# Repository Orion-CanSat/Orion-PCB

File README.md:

# Orion II PCB

&nbsp;
## Who are we?
We are a team composed of 12 students of the [Model High School “Evangeliki Scholi Smyrna”](http://lyk-evsch-n-smyrn.att.sch.gr/wordpress/?p=1322). For the fourth consecutive time we are participating in the Panhellenic competition "[CanSat in Greece](https://cansat.gr/)", a qualifier of the Pan-European competition "[CanSats in Europe](http://www.esa.int/SPECIALS/CanSat/SEMXTDCKP6G_0.html)", organized by ESA (European Space Agency) for the last 8 years. Our team is called Orion II and our supervisor is Dr. Christos Fanidis.

&nbsp;
## Our Inspiration

&nbsp;
## Do you want to contibute?
Unfortuannately this repository does not accept any new commits, or merge requests. You are free to fork it and work on your own.

&nbsp;
## PCB Desgin
These PCBs where designed by Danae Veli.

&nbsp;
## Meet our Team (In alphabetical order)
|                                Name                                |                              Role                              |                                                                                                                                     Introduction                                                                                                                                    |
| ------------------------------------------------------------------ | -------------------------------------------------------------- | ----------------------------------------------------------------------------------------------------------------------------------------------------------------------------------------------------------------------------------------------------------------------------------- |
|                           __Danae Veli__                           |                 Head of Electrical Engineering                 |                               My name is Danae Veli and I am a student at Model High School "Evangeliki Scholi Smyrna". I am a part of team Orion II and I am in charge of the electrical design. My main duty is to design the PCBs for the project.                               |
|   [__Dionysios Angelopoulos__](https://github.com/DennisAngelo)    | Head of Mechanical Engineering and Control Systems Development | My name is Dionysios Angelopoulos. I am a greek High School student attending Model High School “Evangeliki Scholi Smyrna”. I am the head of Mechanical Engineering in Orion II. My main duty was to 3D model the cansat and to design and tune the control system for the cansat.  |
|           [__Jim Balatos__](https://github.com/jbalatos)           |                  Head of Software Engineering                  |                           My name is Jim Balatos. I am a greek High School student attending Model High School “Evangeliki Scholi Smyrna”. I am the head of Software Engineering in Orion II. My main duty was to write the Live Server of our mission.                             |
|                         __Giorgos Kaltsis__                        |                       Senior Data Analyst                      |              |
| [__Konstantinos Kritharidis__](https://github.com/konstantinosk31) |                    Head of Retrieval System                    |               My name is Konstantinos Kritharidis. I am a greek High School student attending The American College of Greece - Pierce. I am the head of the Retrieval System in Orion II. My main duty was to design and create the ram-air parachute for the CanSat.               |
|       [__Rikarnto Bariampa__](https://github.com/richardbar)       |         Head of Telemetry and Senior Software Engineer         |               My name is Rikarnto Bariampa. I am a greek High School student attending Model High School “Evangeliki Scholi Smyrna”. I am the head of Telemetry and a Senior Software Engineer in Orion II. My main duty was to write the onboard code for the CanSat.              |

&nbsp;
## Want to reach us?
If you have any question, please feel free to reach us in one of the following ways:
* [__Email__](mailto:orioncantgr@gmail.com)
* [__Facebook__](https://www.facebook.com/orioncansatteam)
* [__Twitter__](https://twitter.com/OrionCanSat2020)

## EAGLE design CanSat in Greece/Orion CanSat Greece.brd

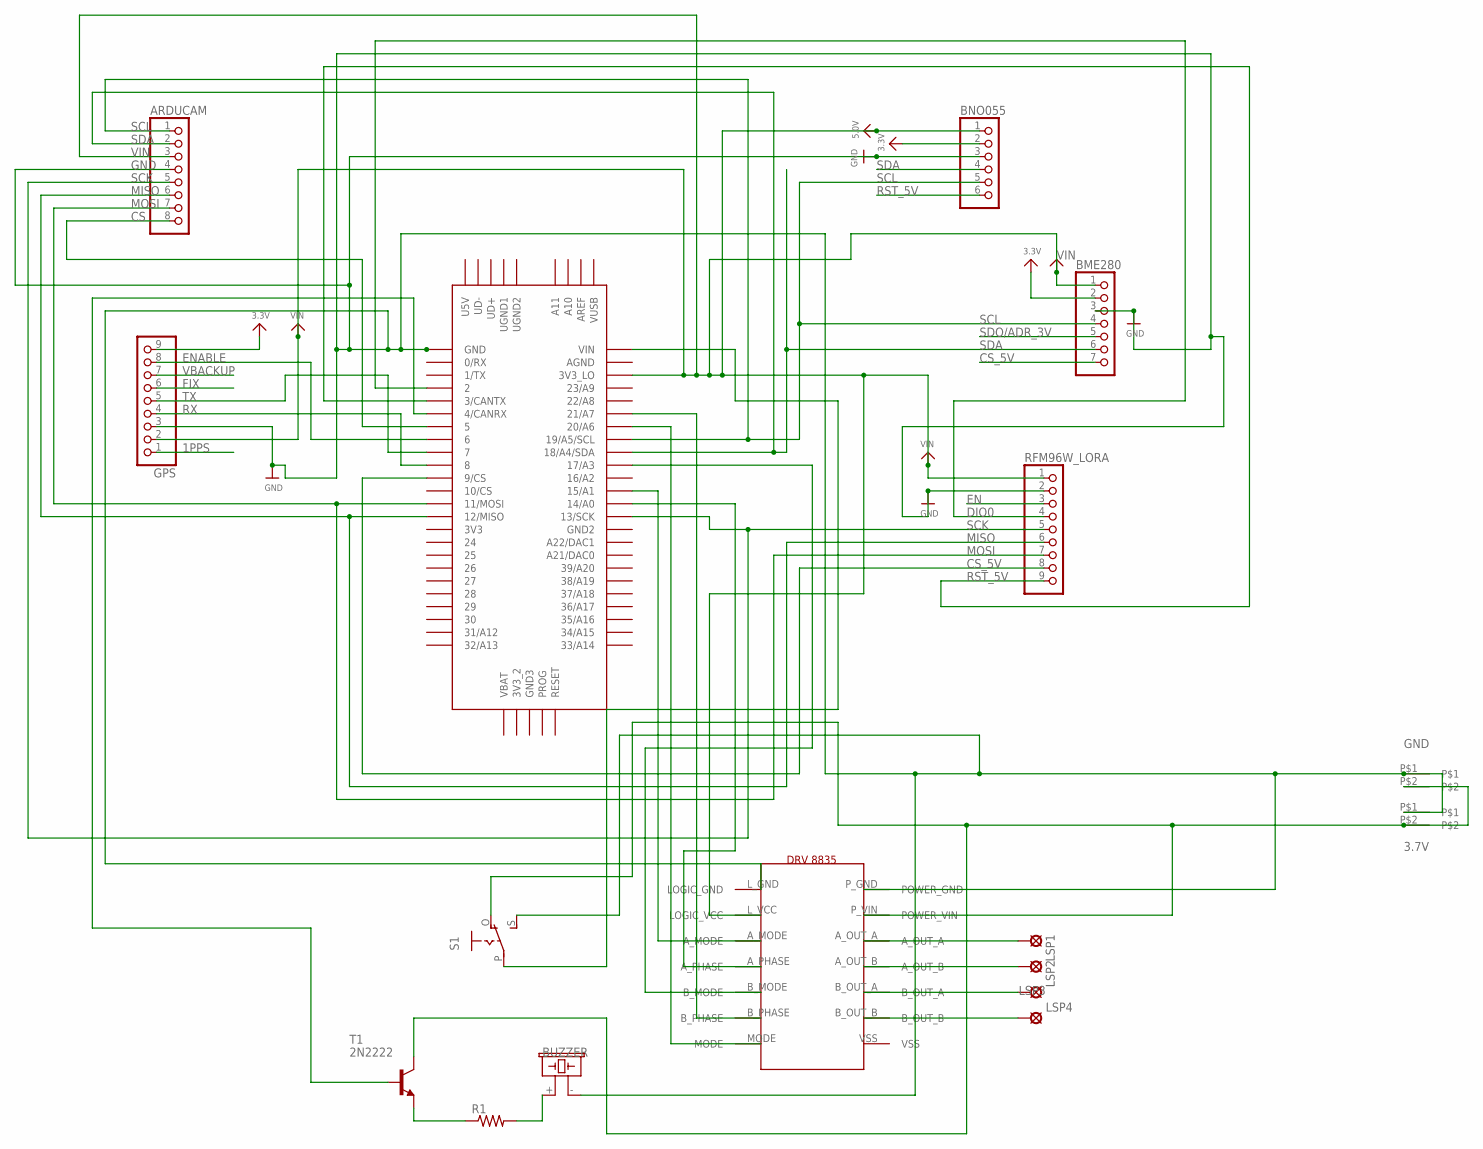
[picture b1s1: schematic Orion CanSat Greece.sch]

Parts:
ARDUCAM: PINHD-1X8BIG; 1X08-BIG
BME280: HEADER-1X770MIL; 1X07_ROUND_70
BNO055: HEADER-1X676MIL; 1X06_ROUND_76
GPS: HEADER-1X970MIL; 1X09_ROUND_70
LSP1, LSP2, LSP3, LSP4: LSP13
R1: FLIPFLOP-RES; 0805-THM
RFM96W_LORA: HEADER-1X970MIL; 1X09_ROUND_70
S1: EG1218S; EG1218
SG2: F/CM12P
T1: 2N2222; TO92-EBC-OVAL
U$1: TEENSY_3.5/3.6
U$7, U$8: 2PINS
U$15: DRV8835

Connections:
1PPS: GPS.1
3.3V: BME280.2, BNO055.2, GPS.9
3V7: S1.P, U$1.VIN
BZPWR: R1.2, SG2.+ (1)
CS: ARDUCAM.8, U$1.5
CS_5V: BME280.7, RFM96W_LORA.8, U$1.9/CS
DIO0: RFM96W_LORA.4, U$1.2
EN: RFM96W_LORA.3
ENABLE: GPS.8, U$1.6
FIX: GPS.6
GND: ARDUCAM.4, BME280.3, BNO055.3, GPS.3, RFM96W_LORA.2, S1.S, SG2.- (2), U$1.GND, U$7.P$1, U$8.P$1, U$15.L_GND (LOGIC_GND), U$15.P_GND (POWER_GND)
MISO: ARDUCAM.6, RFM96W_LORA.6, U$1.12/MISO
MOSI: ARDUCAM.7, RFM96W_LORA.7, U$1.11/MOSI
unnamed: R1.1, T1.E
unnamed: U$1.20/A6, U$15.MODE
unnamed: T1.B, U$1.4/CANRX
unnamed: U$1.21/A7, U$15.B_PHASE
unnamed: U$1.14/A0, U$15.A_PHASE
unnamed: U$1.15/A1, U$15.A_MODE
unnamed: U$1.17/A3, U$15.B_MODE
unnamed: LSP1.MP, U$15.A_OUT_A
unnamed: LSP2.MP, U$15.A_OUT_B
unnamed: LSP3.MP, U$15.B_OUT_A
unnamed: LSP4.MP, U$15.B_OUT_B
RST_5V: BNO055.6, RFM96W_LORA.9, U$1.3/CANTX
RX: GPS.4, U$1.8
SCK: ARDUCAM.5, RFM96W_LORA.5, U$1.13/SCK
SCL: ARDUCAM.1, BME280.4, BNO055.5, U$1.19/A5/SCL
SDA: ARDUCAM.2, BME280.6, BNO055.4, U$1.18/A4/SDA
SDO/ADR_3V: BME280.5
TX: GPS.5, U$1.7
VBACKUP: GPS.7
VBAT: S1.O, T1.C, U$7.P$2, U$8.P$2, U$15.P_VIN (POWER_VIN)
VIN: ARDUCAM.3, BME280.1, BNO055.1, GPS.2, RFM96W_LORA.1, U$1.3V3_LO, U$15.L_VCC (LOGIC_VCC)

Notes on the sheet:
3.7V
GND
BUZZER
VIN

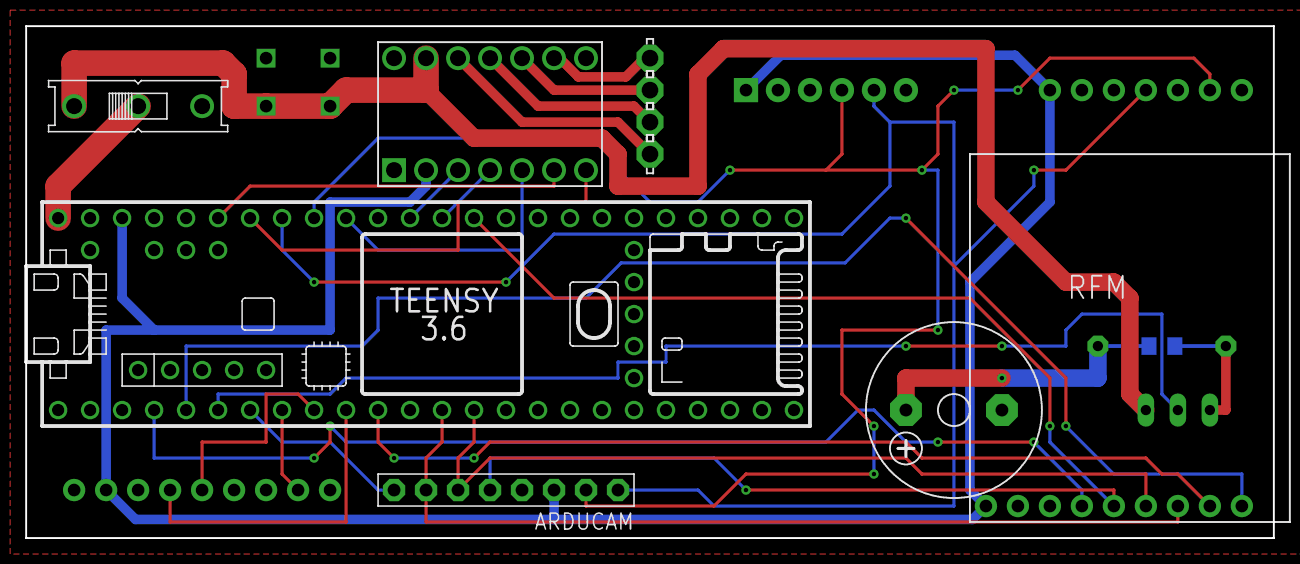
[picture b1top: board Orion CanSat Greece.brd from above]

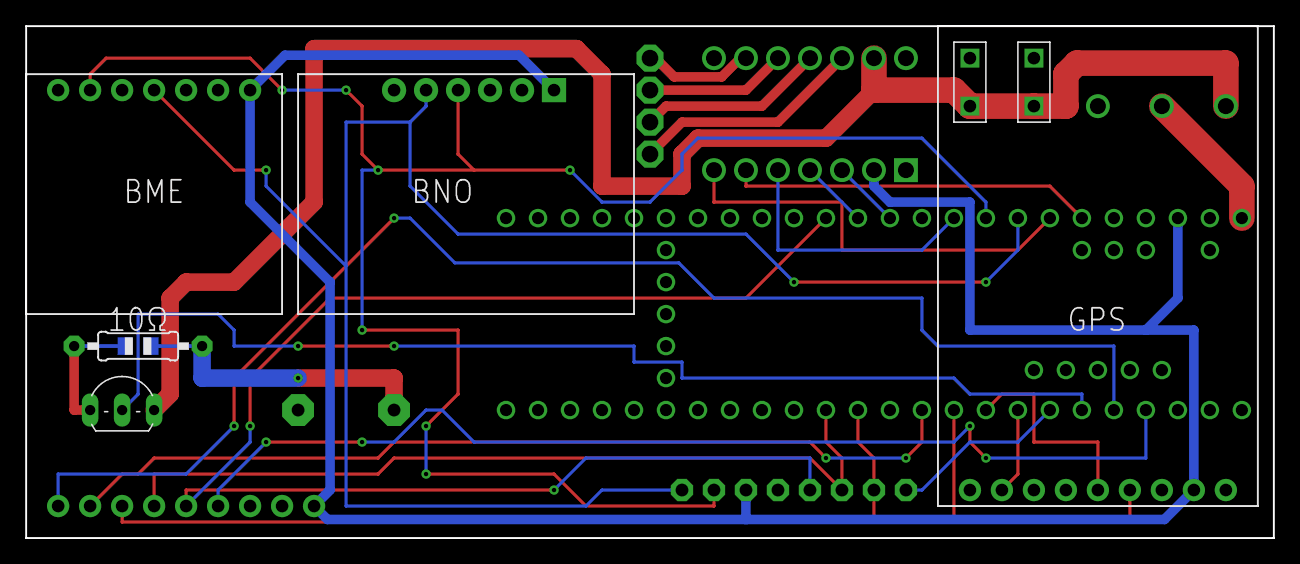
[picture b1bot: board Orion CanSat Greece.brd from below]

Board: 2 copper layers, 99.1 x 40.6 mm, 17 parts (4 on the bottom side), 29 nets.

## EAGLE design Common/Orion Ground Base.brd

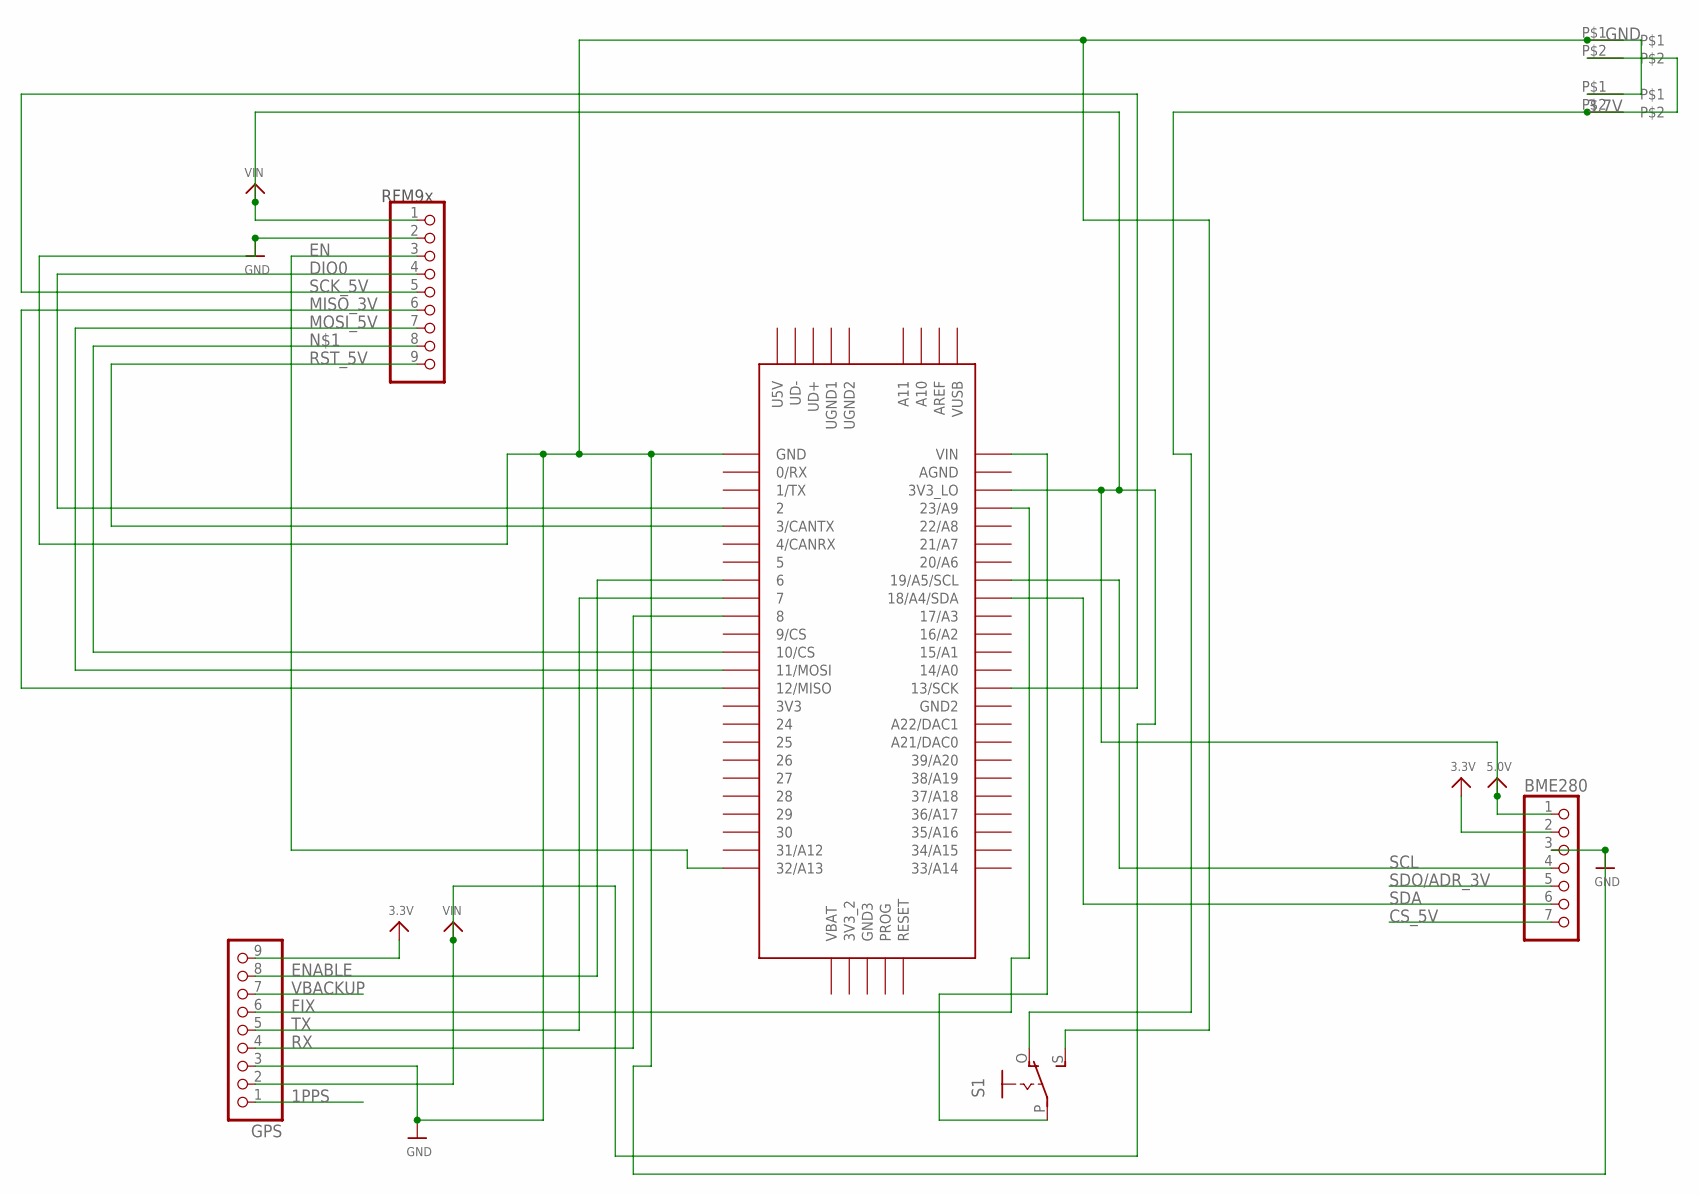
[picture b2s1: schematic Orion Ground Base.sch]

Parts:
BME280: HEADER-1X770MIL; 1X07_ROUND_70
GPS: HEADER-1X970MIL; 1X09_ROUND_70
JP3: HEADER-1X970MIL; 1X09_ROUND_70
S1: EG1218S; EG1218
U$1: TEENSY_3.5/3.6
U$7, U$8: 2PINS

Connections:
1PPS: GPS.1
3.3V: BME280.2, GPS.9
CS_5V: BME280.7
DIO0: JP3.4, U$1.2
EN: JP3.3, U$1.32/A13
ENABLE: GPS.8, U$1.6
FIX: GPS.6, U$1.23/A9
GND: BME280.3, GPS.3, JP3.2, S1.S, U$1.GND, U$7.P$1, U$8.P$1
MISO_3V: JP3.6, U$1.12/MISO
MOSI_5V: JP3.7, U$1.11/MOSI
unnamed: JP3.8, U$1.9/CS, U$1.10/CS
unnamed: S1.P, U$1.VIN
unnamed: S1.O, U$7.P$2, U$8.P$2
RST_5V: JP3.9, U$1.3/CANTX
RX: GPS.4, U$1.8
SCK_5V: JP3.5, U$1.13/SCK
SCL: BME280.4, U$1.19/A5/SCL
SDA: BME280.6, U$1.18/A4/SDA
SDO/ADR_3V: BME280.5
TX: GPS.5, U$1.7
VBACKUP: GPS.7
VIN: BME280.1, GPS.2, JP3.1, U$1.3V3_LO

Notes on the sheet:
RFM9x
3.7V
GND

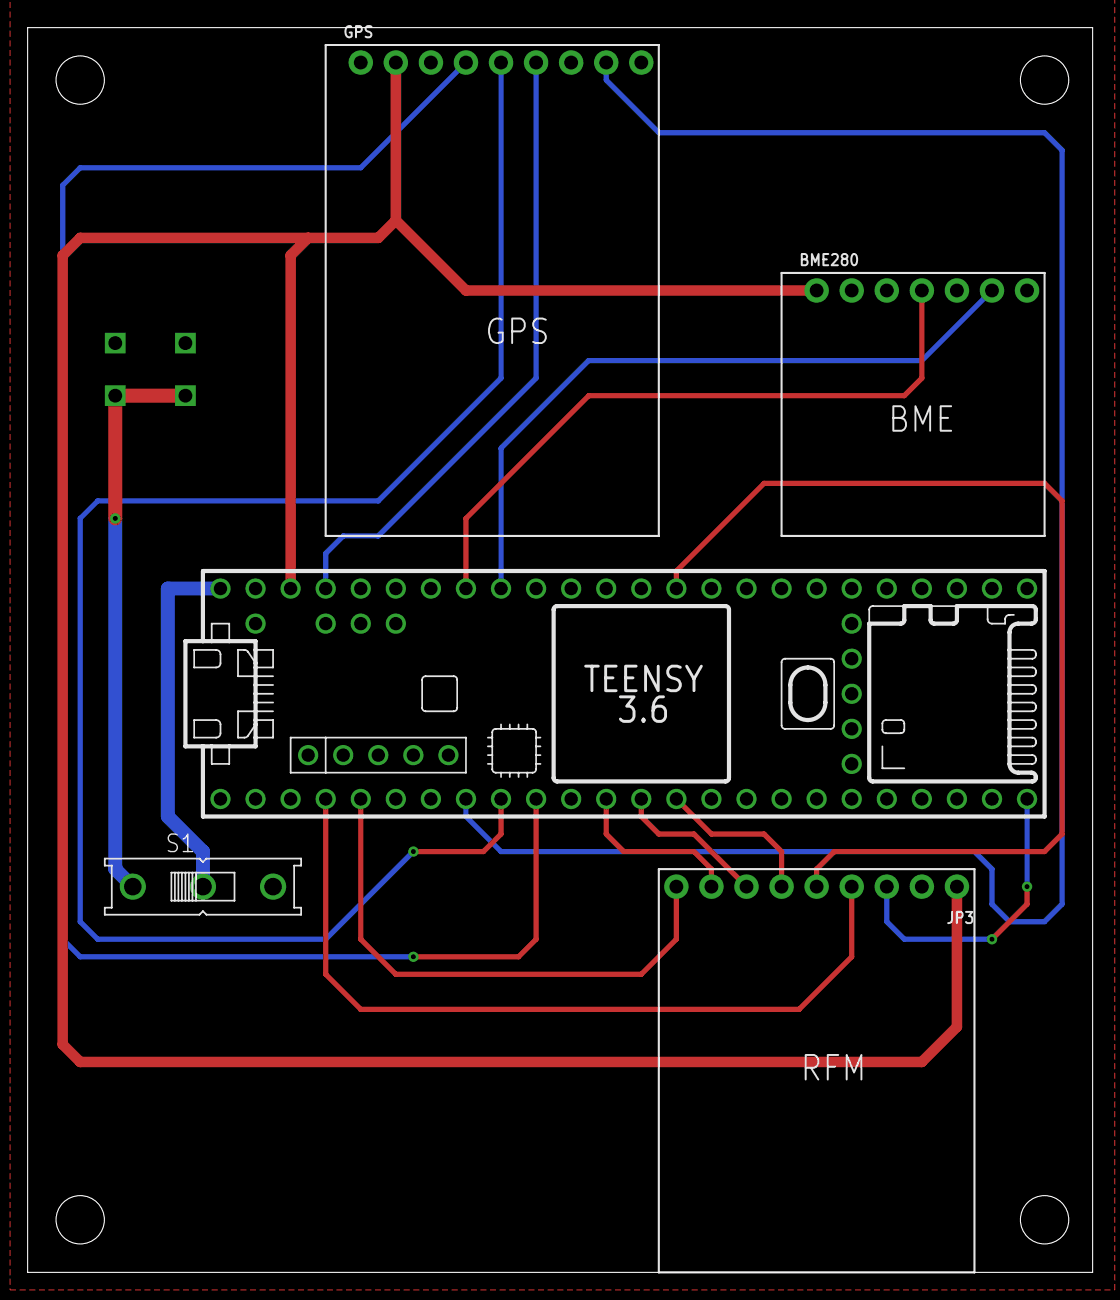
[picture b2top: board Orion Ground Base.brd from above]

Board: 2 copper layers, 77.1 x 90.2 mm, 7 parts (0 on the bottom side), 18 nets.

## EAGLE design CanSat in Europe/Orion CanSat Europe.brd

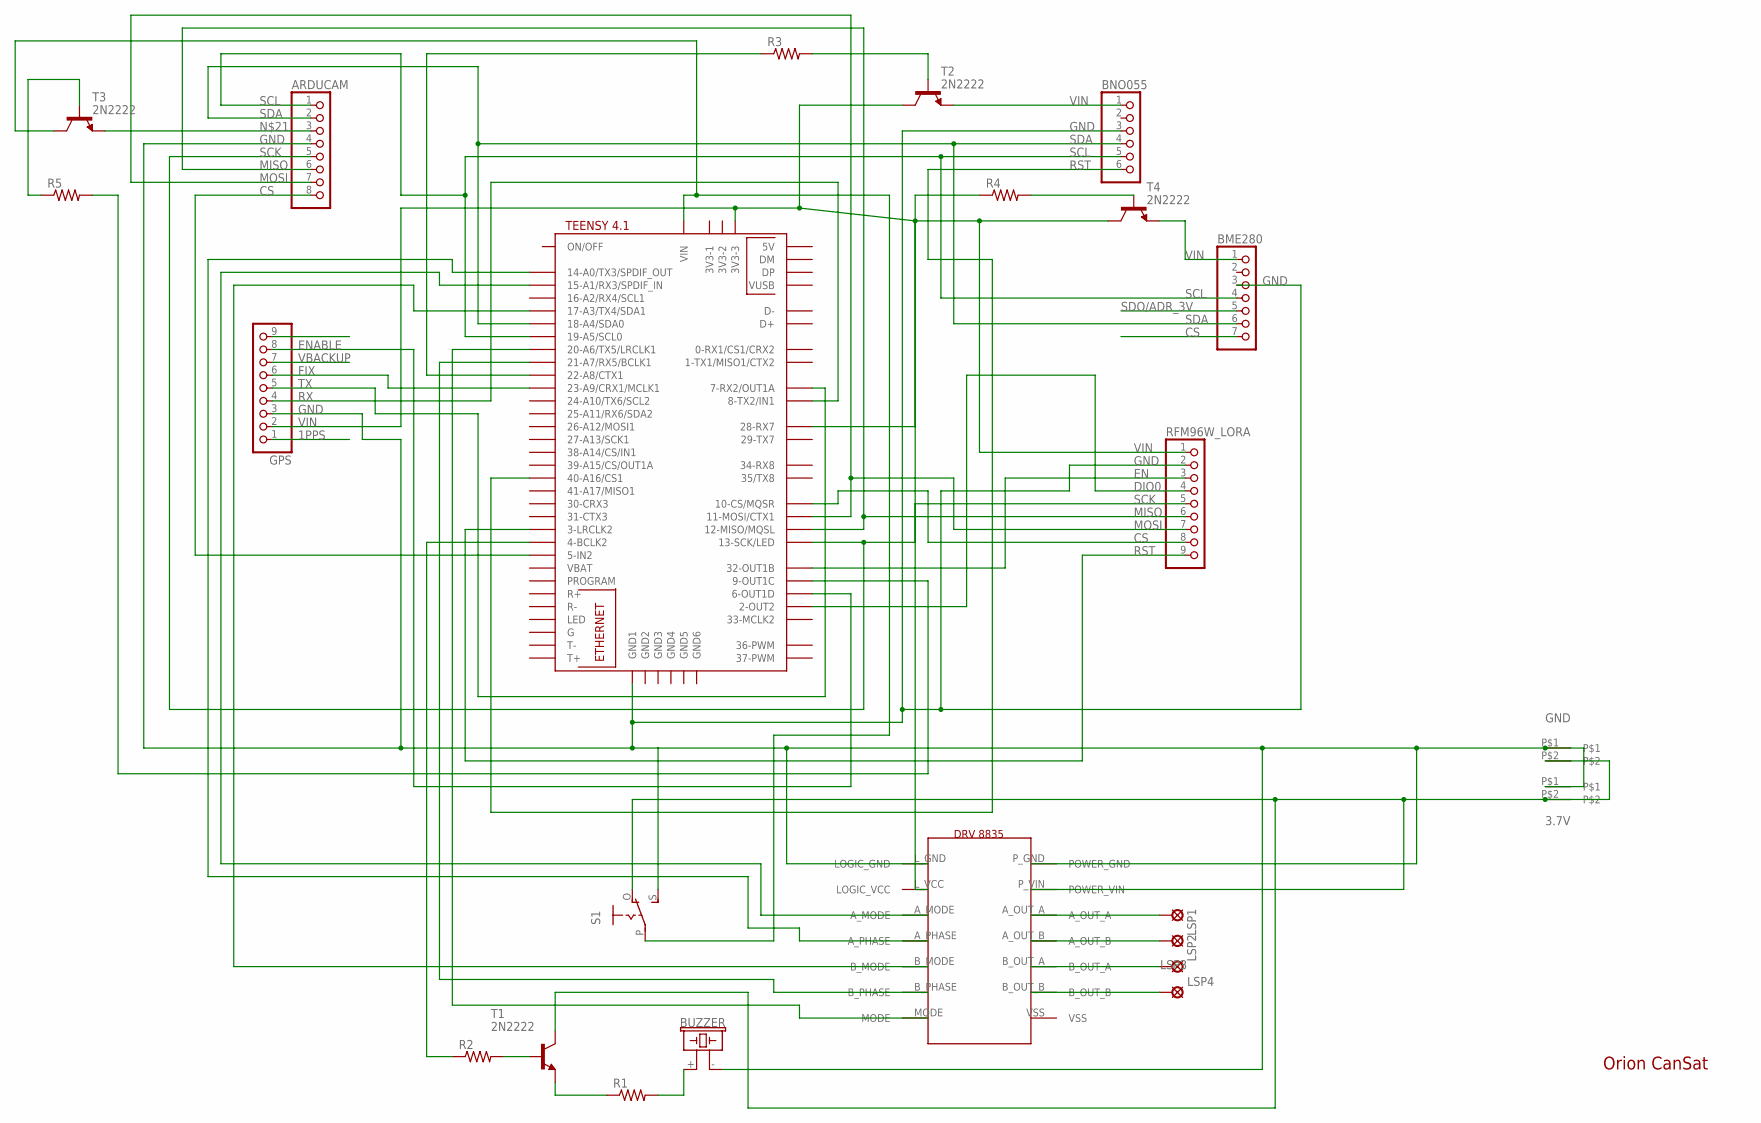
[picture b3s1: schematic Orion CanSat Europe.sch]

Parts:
ARDUCAM: PINHD-1X8BIG; 1X08-BIG
BME280: HEADER-1X770MIL; 1X07_ROUND_70
BNO055: HEADER-1X676MIL; 1X06_ROUND_76
GPS: HEADER-1X970MIL; 1X09_ROUND_70
LSP1, LSP2, LSP3, LSP4: LSP13
R1, R2, R3, R4, R5: FLIPFLOP-RES; 0805-THM
RFM96W_LORA: HEADER-1X970MIL; 1X09_ROUND_70
S1: EG1218S; EG1218
SG2: F/CM12P
T1, T2, T3, T4: 2N2222; TO92-EBC-OVAL
U$1: DRV8835
U$5: TEENSY41
U$7, U$8: 2PINS

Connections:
1PPS: GPS.1
BZPWR: R1.2, SG2.+ (1)
CS: ARDUCAM.8, U$5.5-IN2
CS_5V: BME280.7, RFM96W_LORA.8, U$5.10-CS\MQSR (10-CS/MQSR)
DIO0: RFM96W_LORA.4, U$5.2-OUT2
EN: RFM96W_LORA.3, U$5.32-OUT1B
ENABLE: GPS.8, U$5.6-OUT1D
FIX: GPS.6, U$5.23-A9/CRX1/MCLK1
GND: ARDUCAM.4, BME280.3, BNO055.3, GPS.3, RFM96W_LORA.2, S1.S, SG2.- (2), U$1.L_GND (LOGIC_GND), U$1.P_GND (POWER_GND), U$5.GND1, U$7.P$1, U$8.P$1
MISO: ARDUCAM.6, RFM96W_LORA.6, U$5.12-MISO/MQSL
MOSI: ARDUCAM.7, RFM96W_LORA.7, U$5.11-MOSI/CTX1
unnamed: R1.1, T1.E
unnamed: U$1.MODE, U$5.20-A6/TX5/LRCLK1
unnamed: U$1.A_PHASE, U$5.14-A0/TX3/SPDIF_OUT
unnamed: R3.1, U$5.22-A8/CTX1
unnamed: U$1.B_PHASE, U$5.21-A7/RX5/BCLK1
unnamed: R5.2, U$5.9-OUT1C
unnamed: U$1.A_MODE, U$5.15-A1/RX3/SPDIF_IN
unnamed: R4.1, U$5.28-RX7
unnamed: LSP1.MP, U$1.A_OUT_A
unnamed: R2.2, T1.B
unnamed: LSP2.MP, U$1.A_OUT_B
unnamed: LSP3.MP, U$1.B_OUT_A
unnamed: LSP4.MP, U$1.B_OUT_B
unnamed: R4.2, T4.B
unnamed: R3.2, T2.B
unnamed: GPS.2, RFM96W_LORA.1, T2.C, T4.C, U$1.L_VCC (LOGIC_VCC), U$5.3V3-3
unnamed: U$1.B_MODE, U$5.17-A3/TX4/SDA1
unnamed: BNO055.1, T2.E
unnamed: BME280.1, T4.E
unnamed: ARDUCAM.3, T3.E
unnamed: S1.P, T3.C, U$5.VIN
unnamed: R5.1, T3.B
unnamed: S1.O, T1.C, U$1.P_VIN (POWER_VIN), U$7.P$2, U$8.P$2
unnamed: R2.1, U$5.4-BCLK2
RST: BNO055.6, RFM96W_LORA.9, U$5.3-LRCLK2, U$5.40-A16/CS1
RX: GPS.4, U$5.8-TX2/IN1
SCK: ARDUCAM.5, RFM96W_LORA.5, U$5.13-SCK/LED
SCL: ARDUCAM.1, BME280.4, BNO055.5, U$5.19-A5/SCL0
SDA: ARDUCAM.2, BME280.6, BNO055.4, U$5.18-A4/SDA0
SDO/ADR_3V: BME280.5
TX: GPS.5, U$5.7-RX2/OUT1A
VBACKUP: GPS.7

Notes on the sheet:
3.7V
GND
BUZZER
VIN
Orion CanSat

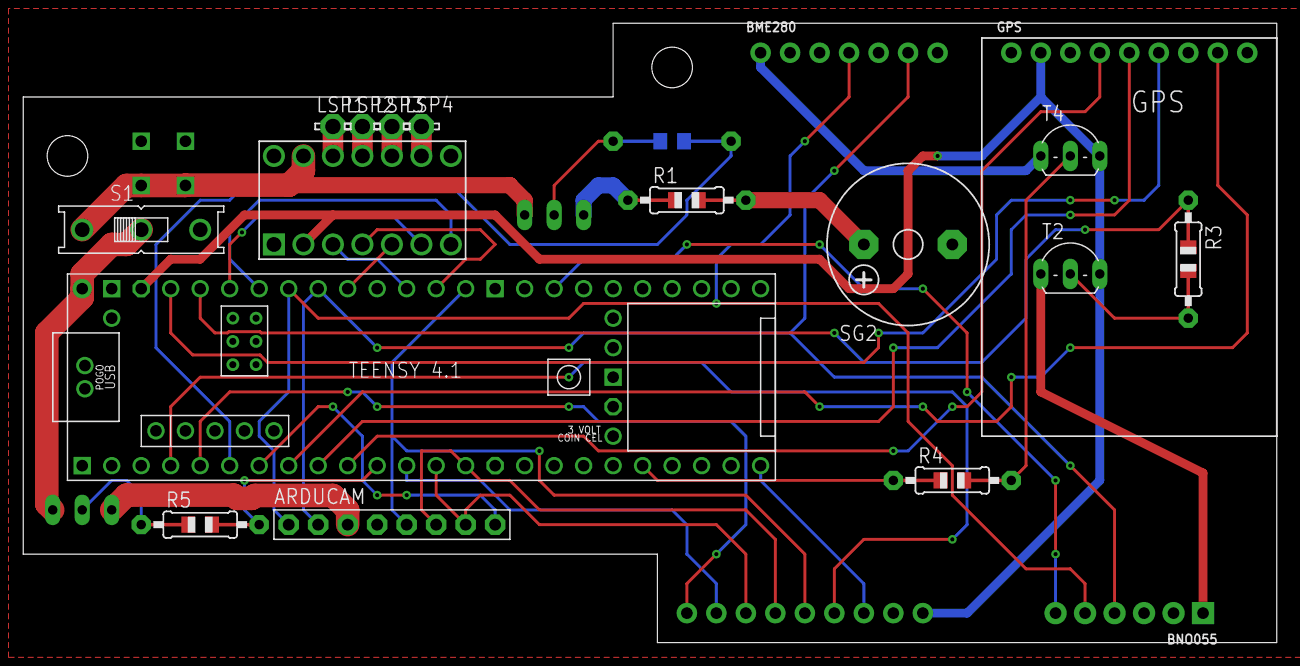
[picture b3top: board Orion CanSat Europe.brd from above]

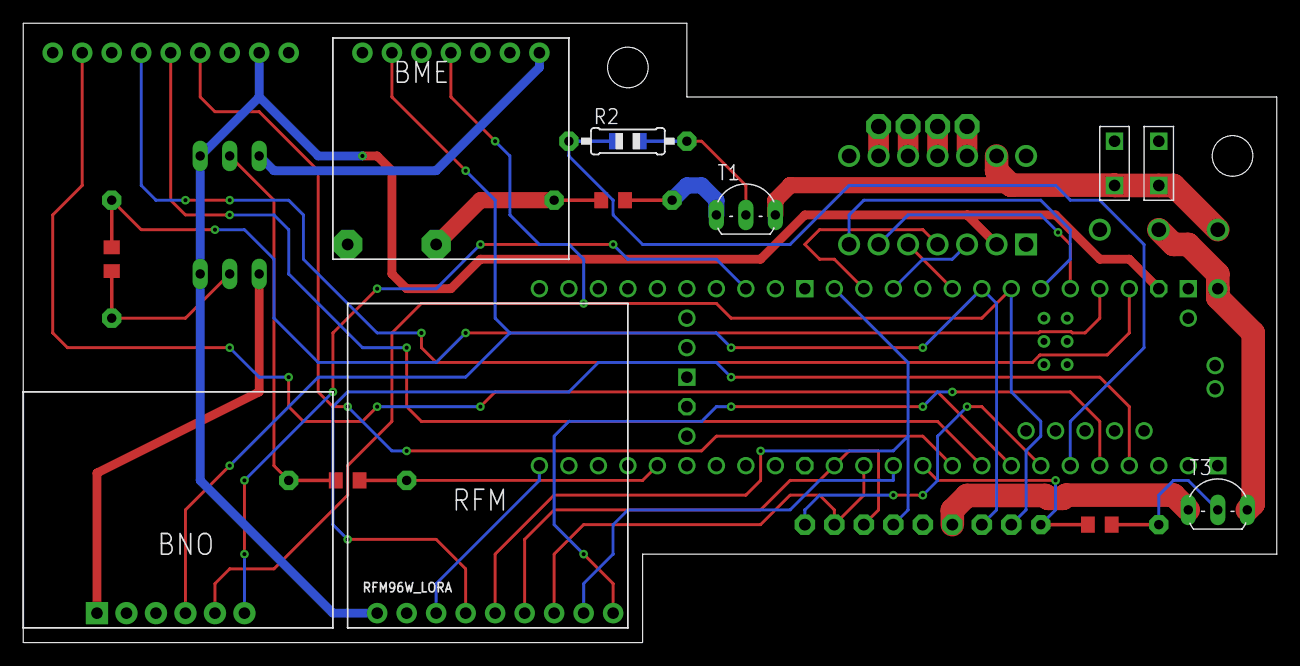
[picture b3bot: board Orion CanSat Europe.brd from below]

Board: 2 copper layers, 108.0 x 53.3 mm, 24 parts (4 on the bottom side), 40 nets.

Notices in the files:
parts and their libraries:
microbuilder: This work is placed in the public domain, and may be freely used for commercial and non-commercial work with the following conditions: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
